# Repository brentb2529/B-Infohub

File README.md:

# B-Infohub

**Local telemetry from a Briggs & Stratton standby generator — no subscription, no cell modem, no cloud.**

A small ESP32 board that plugs into the RS-485 port your generator already has and
speaks Modbus to its GC-1030/1031/1032 controller directly. Home Assistant gets the
readings in about a second, over your own network.

> The InfoHub is not decoding anything proprietary. It is a Modbus master with a cell
> modem and a billing relationship attached. This becomes the master instead — and you
> can keep the InfoHub connected alongside it if you want the cellular path as backup.

---

## What you get

| | EnergyTrak cloud | B-Infohub |
| --- | --- | --- |
| Readings | 34 | **130+** |
| Freshness | minutes | **~1 second** |
| Faults | one "fault" flag | **34 individually decoded alarms** |
| Works without internet | no | **yes** |
| Subscription | yes | no |

Per-leg voltages and currents, kW / kVA / kVAr, power factor, cumulative energy,
coolant temperature, battery voltage, engine RPM and hours, lifetime starts and trips,
the raw controller status word, and each fault condition as its own entity you can
automate on.

It also records alarms to onboard flash, so a fault that happens while Home Assistant
is down or the network is out is still reported when things come back — the one case
cloud monitoring cannot cover.

## What you need

- A Briggs & Stratton standby generator with a **GC-1030, GC-1031 or GC-1032**
  controller (check the label on the panel).
- A **B-Infohub board** — see [Getting the hardware](#getting-the-hardware).
- Home Assistant, with [HACS](https://hacs.xyz) installed.
- A Chrome or Edge browser on a desktop, once, to flash the board.

No soldering. No toolchain. No command line.

## Install

### 1. Flash the board

Connect it to your computer with a **data** USB cable and open the installer:

### → **[Install B-Infohub](https://brentb2529.github.io/B-Infohub/)**

Click Connect, pick the serial port, and wait. The page will then ask for your Wi-Fi.

<sub>A charge-only USB cable is the most common reason nothing appears in the port list —
it powers the board but carries no data, so the board looks dead to the browser while its
power light is on. Web Serial needs Chrome or Edge; Safari and Firefox do not implement it.</sub>

### 2. Wire it to the generator

**Switch the generator to OFF at the panel first.** Two wires, into the RS-485
terminals the controller already exposes — [wiring guide](docs/wiring.md), including
where the terminals are on each controller and how to keep an existing InfoHub
connected at the same time.

### 3. Add it to Home Assistant

Install the **[EnergyTrak integration](https://github.com/brentb2529/ha-energytrak)**
from HACS, then **Settings → Devices & Services → Add Integration → EnergyTrak**.

The bridge is discovered automatically if it is on the same subnet. On a routed or
VLAN'd network — which includes most setups where the generator is on a different
segment — choose **Local B-Infohub bridge** and enter its IP.

You do **not** need an EnergyTrak account. The integration supports three shapes:

- **Bridge only** — no subscription at all
- **Cloud only** — the original behaviour, no hardware
- **Both** — the bridge is used while it is healthy, and the cloud takes over
  automatically if it is not

## Getting the hardware

The board is built in small batches and is **not sold through a shop**. If you want
one, open a [GitHub issue](https://github.com/brentb2529/B-Infohub/issues) or get in
touch — see the ordering note below.

<!-- ORDERING DETAILS: fill these in before publishing.
     - How should people contact you (issue / email / form)?
     - What is supplied: bare PCB, assembled board, assembled + enclosure?
     - Price, and whether shipping is US-only.
     - Any lead time or batch-size caveat. -->

> **Ordering:** _contact details and what is supplied to be filled in._

Everything needed to have one made independently is in this repository —
schematic, layout, gerbers and a JLCPCB-ready fab package in
[`hardware/pcb/`](hardware/pcb/) — and the firmware is MIT licensed. Buying a board
is a convenience, not a requirement.

## It learns the generator it is plugged into

On first healthy contact the bridge probes the controller once — what it
answers, which alarm inputs are wired — and publishes a **Controller
Profile**. Home Assistant shows the learned family as the device model,
plus *Registers present*, *Alarm inputs indeterminate* and *Commissioned*.
**Run Discovery** repeats it. See [`docs/discovery.md`](docs/discovery.md).

## If something looks wrong

The bridge reports its own health, because a monitor that fails silently is worse
than no monitor:

| Entity | What it means when it is unhappy |
| --- | --- |
| **Bridge reachable** | the board is not answering Home Assistant — power or Wi-Fi |
| **Generator answering bus** | the board is fine; the generator has gone quiet on RS-485 |
| **Controller clock age** | the controller is answering but its clock has stopped — it has hung |
| **Bridge silence** | the board holds its connection but has stopped sending |
| **Wi-Fi Signal** | below about −72 dBm an ESP32 stays associated but cannot be reached |

Those are deliberately five separate signals rather than one "online" flag. They fail
independently and each one points at a different place to look.

There are also five LEDs on the board readable through the lid, which is all you have
standing at the generator with no phone signal. [How to read
them](docs/bring-up.md#status-leds).

## Documentation

| | |
| --- | --- |
| [Wiring](docs/wiring.md) | terminals, cable, termination, keeping the InfoHub |
| [Bring-up](docs/bring-up.md) | first boot, LEDs, proving the bus |
| [Register map](docs/register-map.md) | every address, what it means, what it returns |
| [Field findings](docs/field-findings-2026-08-31.md) | what a real controller actually answers |
| [Development](docs/development.md) | building the firmware, the contract, the tooling |

## Safety and scope

A standby generator is life-safety equipment. This is a **read-only monitor**: it does
not start, stop, or configure anything, and engine control is deliberately not
implemented.

Do not rely on it as your only alerting for anything that matters. It is unofficial,
unaffiliated with Briggs & Stratton, and provided as-is under the MIT licence with no
warranty. Wiring anything into a generator is your responsibility; if you are not
comfortable working in the panel, have an electrician do it.

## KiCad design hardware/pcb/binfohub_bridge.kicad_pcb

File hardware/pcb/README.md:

# B-Infohub Bridge v1.1 — PCB

90 × 92 mm, 2-layer, 1.6 mm FR4. KiCad 10 project generated programmatically from
`tools/circuit.py` and verified with `kicad-cli` 10.0.5.

> **Rev 1.1 (2026-10-01) is the current design**: schematic, board, routing, BOM,
> gerbers and the checks below are all rev 1.1. **It fits the rev 1.0 enclosure
> unchanged** — same outline, same six M3 holes, same three terminals on the top
> edge, same LED light-pipe positions. What changed, and why, is in *Rev 1.1*
> below. Rev 1.0 is the fielded board (one unit, running since 2026-09); its files
> are in git history at tag `pcb-rev1.0`.

## Rev 1.1

| Change | Why |
| --- | --- |
| **ESP32-WROOM-32E-H4 soldered**, replacing the socketed DevKitC | Heat. The fielded unit's die ran 125–135 °F at night and 188 °F in afternoon sun, and at 188 °F the controller link dropped a byte per reply (see *Heat*). The -H4 is the −40…+105 °C grade (the plain -32E is rated to 85 °C — the temperature this board has already reached). The DevKit's AMS1117 (5→3.3 V linear, ~0.3 W inside the module footprint) is gone; the module sits on a via-stitched ground pad. |
| **DE pull-downs** (R16/R17, EE review) | The SP3485's DE input has no pull-down and the ESP's GPIOs float from reset until the firmware runs — and for the whole of a J6 first flash. 10 k on each DE keeps both transceivers in receive, so the board can never drive the generator's bus uncommanded. Rev 1.0 is fielded without them. |
| **Single 3.3 V rail** from an AP63203 | The 5 V rail only ever fed that LDO and the PWR LED. Same buck family, pinout and application circuit as the AP63205 it replaces. |
| **Remote-antenna option**: the same pads take the **-32UE** (U.FL) | Antenna end faces the board edge, so only the enclosure wall is in front of it. Order -32E for the internal antenna; -32UE plus a U.FL→SMA bulkhead pigtail if the box is metal or the signal is poor. |
| **J5 fan header**, 12 V PWM (IO32 → AO3400A), 0.5 A polyfuse, SS14 flyback | Only if shading and venting the enclosure are not enough. Firmware `packages/fan.yaml` runs it from the die temperature, Home Assistant or not. |
| **EN/IO0 support, RESET + BOOT buttons, J6 programming header** | A bare module has no USB bridge; J6 is the one USB-serial flash it ever needs. OTA after that, as before. |
| **R10/R11** fail-safe bias on the InfoHub pair | Carried from the 2026-09-28 source-only change — see *Termination*. |
| LED series resistors moved 75 → 77.5 mm; J4 moved to the left edge | Clearing the module's pad row and the antenna region. LEDs themselves have not moved. |

Replaces the Briggs & Stratton InfoHub as the Modbus master on the GC-1032's RS-485
bus, **while passing the InfoHub through on a second port** so its cell modem keeps
working as out-of-band backup during an outage.

| Check (rev 1.1, 2026-10-01) | Result |
| --- | --- |
| `kicad-cli sch erc --severity-all` | **0 violations** (`binfohub_bridge-erc.rpt`) |
| `kicad-cli pcb drc --severity-all --refill-zones --schematic-parity` | **0 errors, 0 unconnected, 0 parity issues** |
| Routing | **100 %**, 0.25 mm-grid A* router, 738 tracks / 109 vias, GND pour both layers **plotted into the gerbers** (see below) |
| LCSC | **36 distinct parts**, one BOM line each; the 11 parts new or changed in rev 1.1 verified in stock on 2026-10-01, the rest last checked 2026-08-31 |

Remaining DRC output is a handful of warnings: short dangling tails on hand-routed
escape stubs the router joined part-way along (low-speed lines, verified
electrically meaningless in the EE review), and `lib_footprint_mismatch` on the
terminal blocks (locating pegs deliberately stripped, see ORDER.md) and on U1
(the project copy of the WROOM footprint, identical to the library on every
pad, via and keepout). **No silk over any pad, no courtyard overlaps.** The exact
counts are in `binfohub_bridge-drc.rpt`.

**EE review (2026-10-01):** independent pre-fab review of the full source; verdict
*green after fixes*, all applied — -H4 module, DE pull-downs, 680 Ω bias, 1.1 A fan
fuse, 100 nF moved to the VDD pad, BOM grouping by part, JLC gerber layer set.
Confirmed clean: every pin against the firmware map, no strapping pins, EN/IO0
reference circuit, buck pinout and FB, D10/Q2 polarity, SM712 pin order, pour
present in the gerbers, antenna keepout honoured.

> **Rev 1.0's shipped gerbers had no ground pour.** `gen_pcb.py` writes zone
> outlines only, and the rev 1.0 plot never refilled them: the F_Cu gerber in git
> history has zero `G36` regions. The fielded board's GND is tracks only — it works,
> but it is not what the README claimed. `tools/export.sh` now plots with
> `--check-zones` and prints the region count so this cannot silently recur.

Everything is regenerated by `tools/export.sh` after `router.py` (or `rebuild.py`
for text-only changes): ERC, DRC, BOM/CPL, gerbers + drill, the JLC zip and the
previews.

## What is on it

| Block | Parts |
| --- | --- |
| **Power in** | J1 screw terminal, AO3401A reverse-polarity P-FET (4 A — carries the InfoHub too), **SMBJ16A TVS**, 100 µF bulk |
| **3.3 V rail** | AP63203WU-7 sync buck, 3.8–32 V in, fixed 3.3 V 2 A + 10 µH shielded inductor (the b-hydro / rev 1.0 circuit; the datasheet's 3.3 V example is 4.7 µH, 10 µH is the conservative side), 1.1 A polyfuse |
| **InfoHub 12 V** | Separate 2 A polyfuse (F2) |
| **Fan 12 V** | J5, separate 1.1 A / 33 V polyfuse (F3 — a PPTC derates ~40 % at box temperature, so 0.5 A would nuisance-trip), AO3400A low-side PWM switch, SS14 flyback |
| **RS-485 × 2** | SP3485EN transceivers, PSM712 TVS per pair, 120 Ω termination on jumpers (ship OPEN — see below); 680 Ω fail-safe bias R10/R11 on the InfoHub pair; 10 k pull-downs on both DE lines so neither transceiver can drive while the ESP is in reset or being flashed |
| **MCU** | ESP32-WROOM-32E**-H4** (−40…+105 °C grade) soldered, or -32UE for U.FL; 10 k/1 µF on EN, RESET and BOOT buttons, J6 programming header |
| **Indicators** | 5 LEDs (PWR / WIFI / BUS / FAULT / TX) sized for light pipes, plus J4 header |

### Why the power section is split into two fuses

Our bridge draws ~150 mA. The InfoHub's cell modem pulses to 1–2 A on transmit. Sharing
a fuse would let an InfoHub fault take down the telemetry — precisely backwards. Both
legs sit behind the same reverse-polarity FET, so a miswired harness cannot hurt either
device, but a fault in one cannot starve the other.

### Why the LED resistors are 100R / 330R and not 1k

These are driven from a 3.3 V GPIO. A blue or green LED has a forward drop near 2.9 V,
leaving ~0.4 V across the resistor — 1k would give roughly **0.5 mA**, invisible through
a light pipe. 100R for blue/green and 330R for red/yellow puts all five at about 4 mA.

## Termination: ship JP1 and JP2 OPEN

Measured, not assumed. On 2026-08-31 the live bus delivered **368 consecutive
error-free 87-register block reads** (32,016 values, every one CRC-checked) across
engine cranking and five minutes of running, with an adapter that was almost certainly
unterminated. Zero failures.

The physics agrees. At 9600 baud one bit is **104 µs**; signal propagates at ~5 ns/m,
so even a 30 m run has a 150 ns round trip — 0.14 % of a bit period. Reflections from
the SP3485's fast edges settle within a few hundred nanoseconds, while the receiver
samples in the *middle* of the bit. Termination is governed by edge rate versus cable
delay, and here there are three orders of magnitude of margin.

There is also a cost to fitting them: 120 Ω with no fail-safe biasing pulls A and B
together at idle, which can leave the receiver output indeterminate and produce framing
errors. **Adding termination to a bus that already works can make idle behaviour
worse.**

So: leave both jumpers open. Fit one only if CRC errors appear on that segment. They
exist so the option is available, not because it is needed.

If a bus ever does misbehave at idle rather than in traffic, the fix is fail-safe
biasing (pull-up on A, pull-down on B), not termination.

**Rev 1.0 has no bias footprints, and port B does misbehave at idle.** A raw-frame
capture on 2026-09-28 showed ~61 bytes of garbage arriving on the InfoHub pair 35–57 ms
after every reply the bridge sends — the pair floating inside the receiver's ±200 mV
dead band once our driver releases it. ESPHome's Modbus server reads that as an
incoming request, holds its next reply, and drops it: 8 of 36 replies to the InfoHub
in 75 s, with the InfoHub retrying after 0.8 s each time. It tolerates this (it kept
the vendor cloud fed for a week on it), but the bus is dirtier than it should be. Port
A is unaffected because the GC-1032 biases its own bus.

**Rev 1.1 adds R10/R11** (4.7 kΩ pull-up on A to 3.3 V, pull-down on B to GND, next
to U4), fitted by default. Rev 1.0 boards are left as they are by decision; the
firmware can be made tolerant of the noise (flush the port-B receive buffer after
transmitting) if a fielded board ever needs it.

## Heat — measured on the fielded unit, 2026-10-01

The ESP32 die runs **125–135 °F at night** with the air in the 50s: ~75 °F of
self-heating in a sealed box with no airflow. A clear afternoon adds **45–60 °F**
of solar gain on the enclosure (overcast days add 8–17 °F), and the peak is always
13:30–14:45 regardless of the air temperature. On 1 Oct, 80 °F air put the die at
**188 °F**; the port-A link to the GC-1032 then dropped one byte from every reply
(0 good reads for ~90 min, reproduced on a fresh boot at the same temperature) and
recovered on its own as the box cooled. 185 °F on 25 Sep had survived, so the cliff
is ~185–188 °F die. Which end of the link drifts first is not known; the SP3485EN
is industrial grade (−40…+85 °C), the controller is in the same sun.

Firmware 1.2.1 took the two biggest self-heat terms down (CPU 240→160 MHz, Wi-Fi
modem sleep): die fell 192→162 °F in four minutes in the same sun. HA automation
`binfohub_bridge_hot` warns at 175 °F. Neither is the fix; the enclosure is.

**In order of effect:**

1. **Mounting note on the enclosure and in the install guide: not in direct
   afternoon sun.** Shade (a louvered shroud, or the north side of the pad) is
   worth more than every item below combined — it is the ~55 °F term.
2. **A breathing enclosure.** The rev 1.0 box has one membrane vent, low, and
   still reached 188 °F: one vent does not convect. Add a second Gore-type vent
   **high** on the opposite wall so the box is a chimney. Passive; no moving parts
   on a box that must run through an outage.
3. **Done in rev 1.1: bare ESP32-WROOM-32E on the board, 3.3 V straight from an
   AP63203 buck.** The DevKit's AMS1117 LDO dissipated ~0.3 W dropping 5→3.3 V
   inside the module footprint; the module now sits on a via-stitched ground pad
   into the back-side pour.
4. **Fan — provided for, not fitted.** Rev 1.1 carries J5 (12 V, PWM, fused,
   flyback) so a fan can be added without a board change if 1–3 are not enough.
   A fan is a moving part, a dust and moisture path, and a load on the
   generator-side 12 V; a heatsink in still, trapped air moves heat into the same
   air. Neither is the first answer.

Acceptance test: a sunny-afternoon die peak at least 20 °F under the 175 °F
alert, i.e. the rev 1.1 unit should never page.

## Bus parameters — measured, not assumed

**Slave 10, 9600 8E1.** Not the genmon defaults (1 / 19200). Found with
`tools/gc1032_probe.py scan` on 2026-08-31 and confirmed against live readings; the
values are on the back silkscreen so nobody has to re-derive them. See
`../../docs/field-findings-2026-08-31.md`.

## Enclosure interface

The lid needs light pipes over these LED centres (board coordinates, origin = top-left):

| LED | Function | Colour | x | y |
| --- | --- | --- | --- | --- |
| D5 | PWR | green | 18.0 | 80.0 |
| D6 | WIFI | blue | 29.0 | 80.0 |
| D7 | BUS | green | 40.0 | 80.0 |
| D8 | FAULT | red | 51.0 | 80.0 |
| D9 | TX | yellow | 62.0 | 80.0 |

11 mm pitch, which suits 3 mm acrylic rod.

**Cable entry.** All three terminals sit on the **top edge (y = 7)** with their wire
openings facing outward, so one enclosure wall takes every gland. Pad spans:

| Terminal | x range |
| --- | --- |
| J1 12 V IN (2P, 5.08 mm) | 12.0 – 17.1 |
| J2 BUS (2P, 2.54 mm) | 50.0 – 52.5 |
| J3 INFOHUB (4P, 2.54 mm) | 70.0 – 77.6 |

**Terminal contents.** The generator harness carries four conductors that matter:
+12 V, GND, and the RS-485 pair. Power lands on J1, the pair lands on J2 — and J2
needs no ground pin of its own, because the harness ground is already on J1 and it is
the same net. J3 is different: it is a separate cable run out to the InfoHub carrying
power *and* data, so it needs its own return.

| | Pins | To |
| --- | --- | --- |
| J1 | +12V, GND | harness power (red/grey, black) |
| J2 | A, B | harness RS-485 pair (brown, yellow) |
| J3 | +12V, GND, A, B | the InfoHub |

**Mounting:** six M3 holes at (4.5, 4.5), (85.5, 4.5), (4.5, 46), (85.5, 46),
(4.5, 87.5), (85.5, 87.5).

## Files

| File | Purpose |
| --- | --- |
| `binfohub_bridge.kicad_pro/.kicad_sch/.kicad_pcb` | KiCad project |
| `binfohub.kicad_sym`, `binfohub.pretty/` | ESP32-DevKitC-38 symbol + footprint |
| `binfohub_bridge_jlc.zip` | Gerber X2 + Excellon — upload as-is |
| `bom_jlc.csv`, `cpl_jlc.csv` | JLCPCB BOM (verified LCSC numbers) and pick-and-place |
| `ORDER.md` | What to upload, board options, and the loose parts JLC will not place |
| `preview/silk_front-1.png` | Readable silkscreen plot |
| `preview/top.png`, `schematic.pdf` | Render and schematic |
| `tools/` | `circuit.py` is the single source of truth |

Regenerate: `cd tools && python3 gen_libs.py && python3 gen_sch.py && python3 router.py && python3 gen_bom.py`

## Two fixes made to the inherited b-hydro tooling

**`router.py` — trapped-pad escapes.** A pad ringed by its neighbours' keepouts
(SOIC-8 at 1.27 mm, TSOT-23-6) has no free cell for A* to start from. `prelinks`
extended only the *target* set, which helps the far end of a net and does nothing for
the pad that is actually stuck. It now seeds the *source* side too. This took routing
from 11 failures to 0.

**`router.py` — mounting keepouts.** Were hard-coded to b-hydro's 120 × 90 corners, so
two keepouts sat off this board and two real holes had none.

## Before ordering

Not yet reviewed by a second pair of eyes. Specifically worth checking:

- **SM712 pin mapping.** KiCad's `SM712_SOT23` symbol has pin 3 as common; confirm
  against the PSM712 datasheet before fab. Getting it wrong makes the TVS useless.
- Terminal-block orientation (the 180° post-pass in `circuit.py`) — this is the exact
  issue JLC's DFM review flagged on b-hydro.
- AP63205 application circuit against its datasheet, though it is unchanged from a
  board that has already been built.

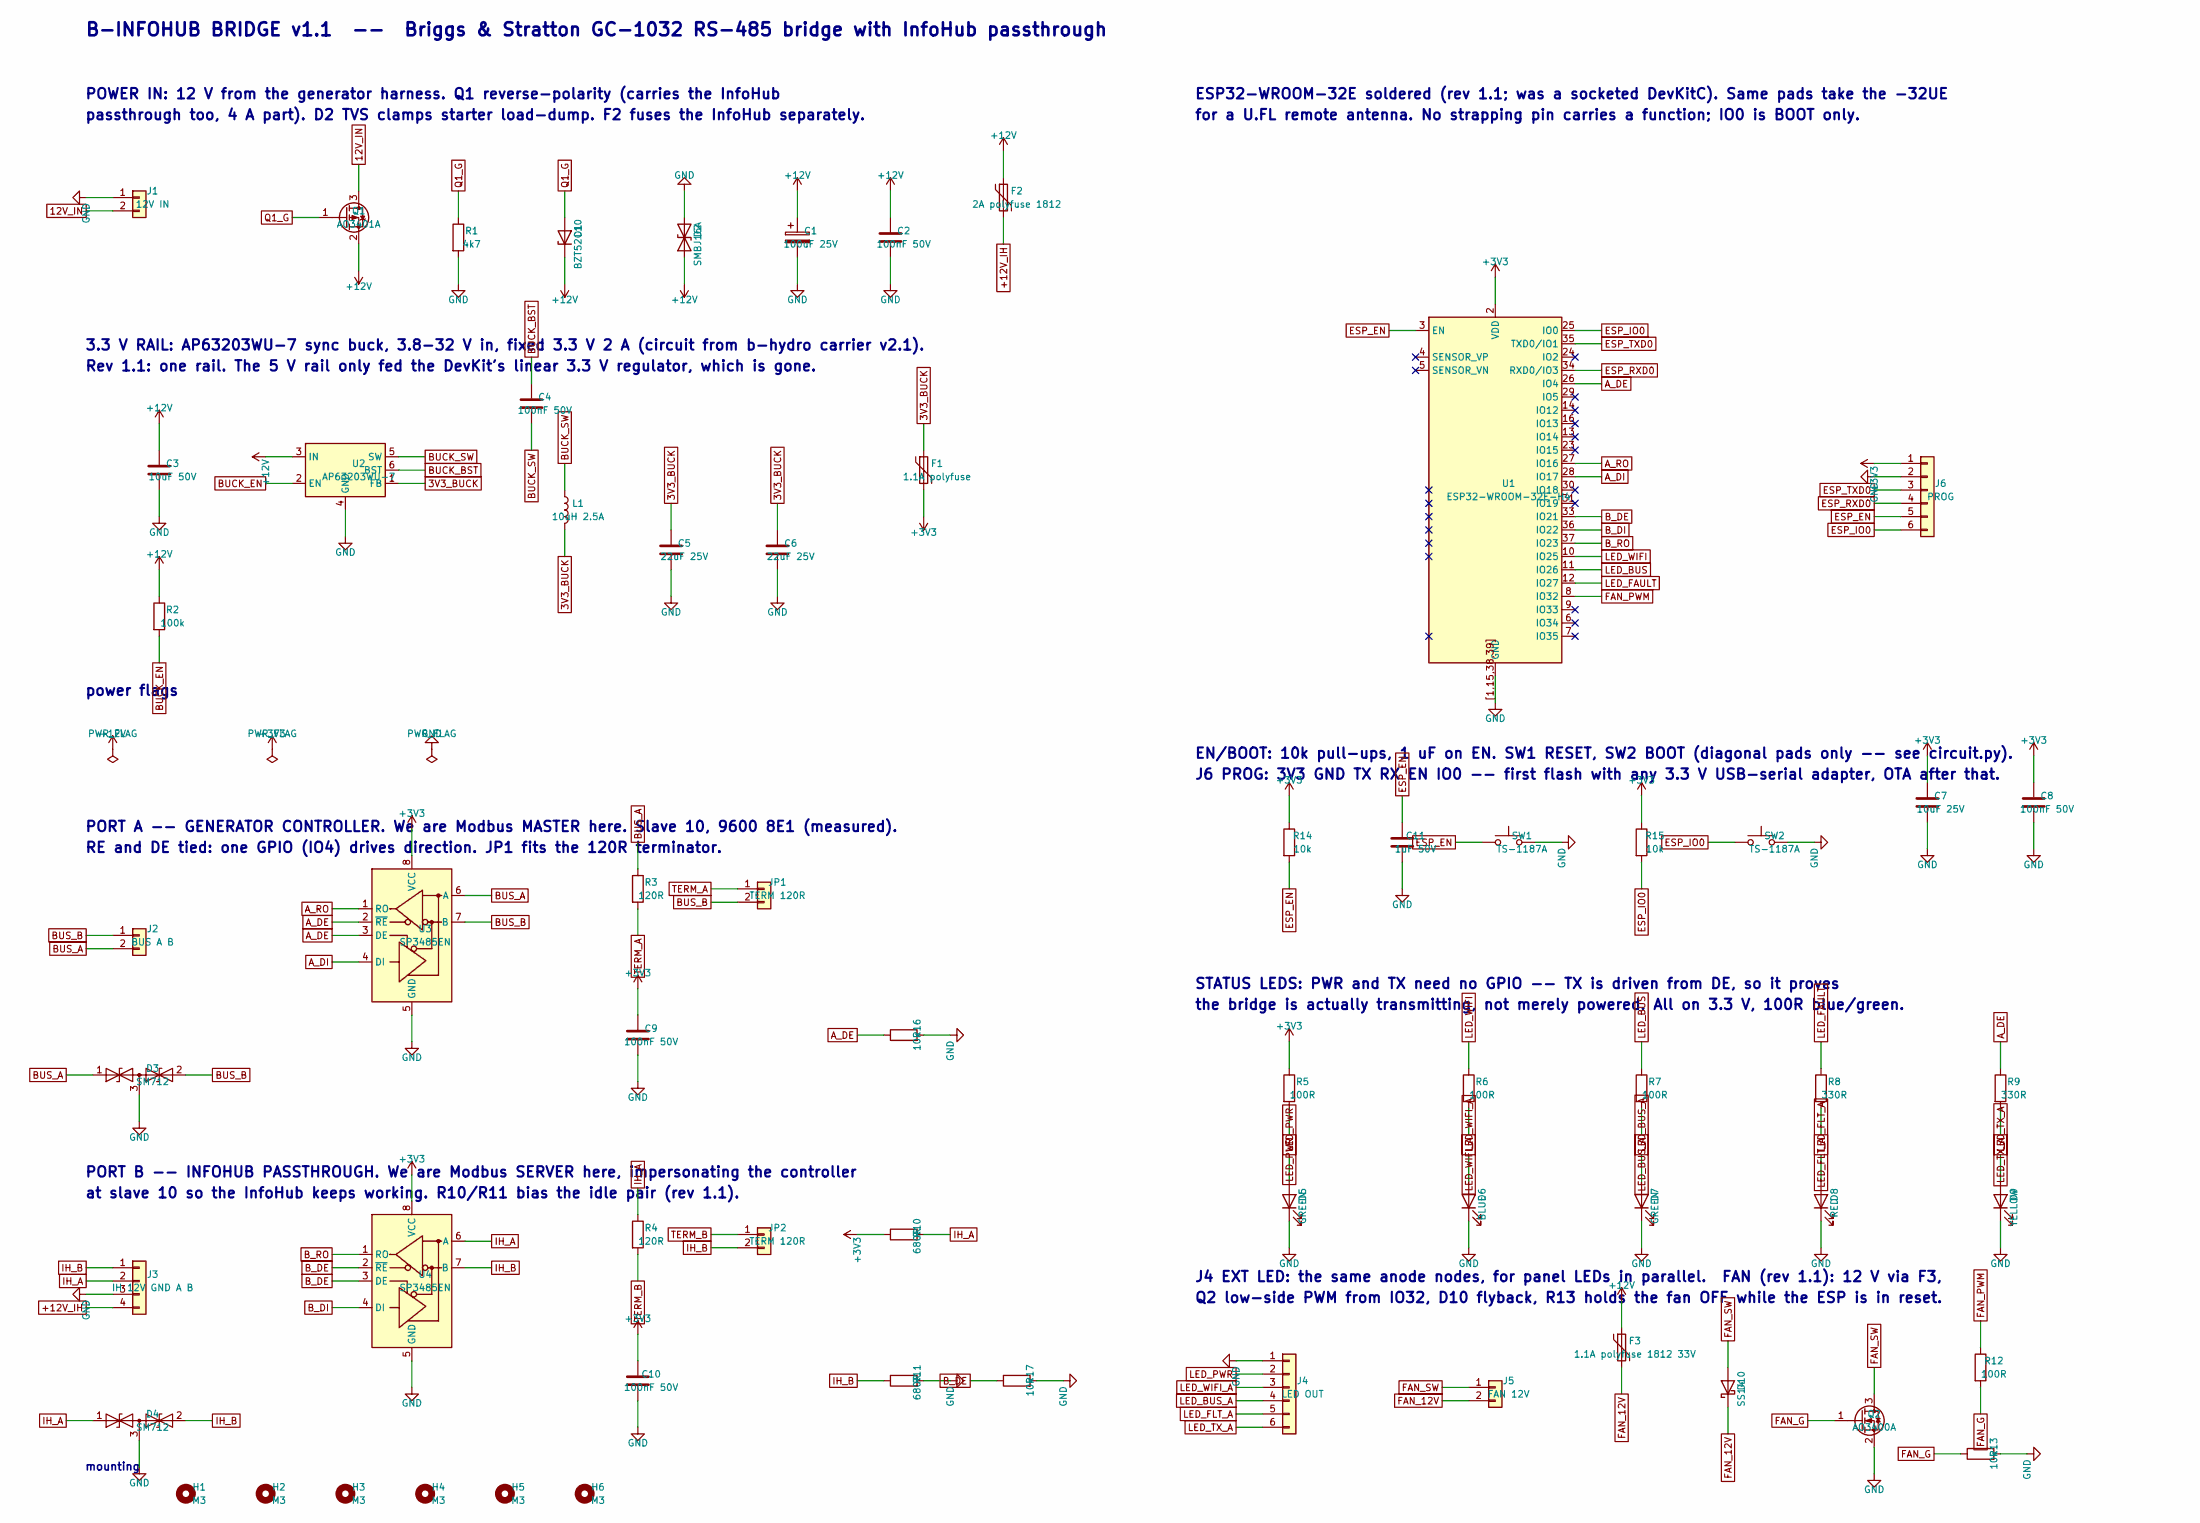
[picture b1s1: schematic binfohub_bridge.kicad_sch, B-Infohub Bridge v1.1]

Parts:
C1: 100uF 25V; CP_Elec_6.3x7.7; LCSC C3338
C2, C4, C8, C9, C10: 100nF 50V; C_0603_1608Metric; LCSC C14663
C3: 10uF 50V; C_1206_3216Metric; LCSC C13585
C5, C6: 22uF 25V; C_0805_2012Metric; LCSC C45783
C7: 10uF 25V; C_0805_2012Metric; LCSC C15850
C11: 1uF 50V; C_0603_1608Metric; LCSC C15849
D1: BZT52C10; D_SOD-123; LCSC C173431
D2: SMBJ16A; D_SMB; LCSC C353386
D3, D4: SM712; SOT-23; LCSC C32677
D5, D7: GREEN; LED_0603_1608Metric; LCSC C965804
D6: BLUE; LED_0603_1608Metric; LCSC C965807
D8: RED; LED_0603_1608Metric; LCSC C2286
D9: YELLOW; LED_0603_1608Metric; LCSC C965803
D10: SS14; D_SMA; LCSC C2480
F1: 1.1A polyfuse; Fuse_1812_4532Metric; LCSC C883148
F2: 2A polyfuse 1812; Fuse_1812_4532Metric; LCSC C2760293
F3: 1.1A polyfuse 1812 33V; Fuse_1812_4532Metric; LCSC C142747
H1, H2, H3, H4, H5, H6: M3; MountingHole_3.2mm_M3
J1: 12V IN; TerminalBlock_Phoenix_MKDS-1,5-2-5.08_1x02_P5.08mm_Horizont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; LCSC C474881
J2: BUS A B; TerminalBlock_Phoenix_MPT-0,5-2-2.54_1x02_P2.54mm_Horizontal; LCSC C474920
J3: IH 12V GND A B; TerminalBlock_Phoenix_MPT-0,5-4-2.54_1x04_P2.54mm_Horizontal; LCSC C474922
J4: LED OUT; PinHeader_1x06_P2.54mm_Vertical; LCSC C492405
J5: FAN 12V; TerminalBlock_Phoenix_MPT-0,5-2-2.54_1x02_P2.54mm_Horizontal; LCSC C474920
J6: PROG; PinHeader_1x06_P2.54mm_Vertical; LCSC C492405
JP1, JP2: TERM 120R; PinHeader_1x02_P2.54mm_Vertical; LCSC C492401
L1: 10uH 2.5A; L_Bourns_SRN6045TA; LCSC C79272
Q1: AO3401A; SOT-23; LCSC C15127
Q2: AO3400A; SOT-23; LCSC C20917
R1: 4k7; R_0603_1608Metric; LCSC C23162
R2: 100k; R_0603_1608Metric; LCSC C25803
R3, R4: 120R; R_0603_1608Metric; LCSC C22787
R5, R6, R7, R12: 100R; R_0603_1608Metric; LCSC C22775
R8, R9: 330R; R_0603_1608Metric; LCSC C23138
R10, R11: 680R; R_0603_1608Metric; LCSC C23228
R13, R14, R15, R16, R17: 10k; R_0603_1608Metric; LCSC C25804
SW1, SW2: TS-1187A; SW_TS-1187A; LCSC C318884
U1: ESP32-WROOM-32E-H4; ESP32-WROOM-32E_edge; LCSC C3013935
U2: AP63203WU-7; TSOT-23-6; LCSC C780769
U3, U4: SP3485EN; SOIC-8_3.9x4.9mm_P1.27mm; LCSC C8963

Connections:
3V3_BUCK: C5.1, C6.1, F1.1, L1.2, U2.1 (FB)
12V_IN: J1.2, Q1.3 (D)
+3V3: C7.1, C8.1, C9.1, C10.1, F1.2, J6.1, R5.1, R10.1, R14.1, R15.1, U1.2 (VDD), U3.8 (VCC), U4.8 (VCC)
+12V: C1.1, C2.1, C3.1, D1.1 (K), D2.1 (A1), F2.1, F3.1, Q1.2 (S), R2.1, U2.3 (IN)
+12V_IH: F2.2, J3.4
A_DE: R9.1, R16.1, U1.26 (IO4), U3.2 (~RE), U3.3 (DE)
A_DI: U1.28 (IO17), U3.4 (DI)
A_RO: U1.27 (IO16), U3.1 (RO)
BUCK_BST: C4.1, U2.6 (BST)
BUCK_EN: R2.2, U2.2 (EN)
BUCK_SW: C4.2, L1.1, U2.5 (SW)
BUS_A: D3.1 (A1), J2.2, R3.1, U3.6 (A)
BUS_B: D3.2 (A2), J2.1, JP1.2, U3.7 (B)
B_DE: R17.1, U1.33 (IO21), U4.2 (~RE), U4.3 (DE)
B_DI: U1.36 (IO22), U4.4 (DI)
B_RO: U1.37 (IO23), U4.1 (RO)
ESP_EN: C11.1, J6.5, R14.2, SW1.1, U1.3 (EN)
ESP_IO0: J6.6, R15.2, SW2.1, U1.25 (IO0)
ESP_RXD0: J6.4, U1.34 (RXD0/IO3)
ESP_TXD0: J6.3, U1.35 (TXD0/IO1)
FAN_12V: D10.1 (K), F3.2, J5.2
FAN_G: Q2.1 (G), R12.2, R13.1
FAN_PWM: R12.1, U1.8 (IO32)
FAN_SW: D10.2 (A), J5.1, Q2.3 (D)
GND: C1.2, C2.2, C3.2, C5.2, C6.2, C7.2, C8.2, C9.2, C10.2, C11.2, D2.2 (A2), D3.3 (common), D4.3 (common), D5.1 (K), D6.1 (K), D7.1 (K), D8.1 (K), D9.1 (K), J1.1, J3.3, J4.1, J6.2, Q2.2 (S), R1.2, R11.2, R13.2, R16.2, R17.2, SW1.2, SW2.2, U1.1, U1.15, U1.38, U1.39, U1.[1,15,38,39] (GND), U2.4 (GND), U3.5 (GND), U4.5 (GND)
IH_A: D4.1 (A1), J3.2, R4.1, R10.2, U4.6 (A)
IH_B: D4.2 (A2), J3.1, JP2.2, R11.1, U4.7 (B)
LED_BUS: R7.1, U1.11 (IO26)
LED_BUS_A: D7.2 (A), J4.4, R7.2
LED_FAULT: R8.1, U1.12 (IO27)
LED_FLT_A: D8.2 (A), J4.5, R8.2
LED_PWR: D5.2 (A), J4.2, R5.2
LED_TX_A: D9.2 (A), J4.6, R9.2
LED_WIFI: R6.1, U1.10 (IO25)
LED_WIFI_A: D6.2 (A), J4.3, R6.2
Q1_G: D1.2 (A), Q1.1 (G), R1.1
TERM_A: JP1.1, R3.2
TERM_B: JP2.1, R4.2

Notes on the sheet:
B-INFOHUB BRIDGE v1.1 -- Briggs & Stratton GC-1032 RS-485 bridge with InfoHub passthrough
POWER IN: 12 V from the generator harness. Q1 reverse-polarity (carries the InfoHub
passthrough too, 4 A part). D2 TVS clamps starter load-dump. F2 fuses the InfoHub separately.
3.3 V RAIL: AP63203WU-7 sync buck, 3.8-32 V in, fixed 3.3 V 2 A (circuit from b-hydro carrier v2.1).
Rev 1.1: one rail. The 5 V rail only fed the DevKit's linear 3.3 V regulator, which is gone.
power flags
PORT A -- GENERATOR CONTROLLER. We are Modbus MASTER here. Slave 10, 9600 8E1 (measured).
RE and DE tied: one GPIO (IO4) drives direction. JP1 fits the 120R terminator.
PORT B -- INFOHUB PASSTHROUGH. We are Modbus SERVER here, impersonating the controller
at slave 10 so the InfoHub keeps working. R10/R11 bias the idle pair (rev 1.1).
mounting
ESP32-WROOM-32E soldered (rev 1.1; was a socketed DevKitC). Same pads take the -32UE
for a U.FL remote antenna. No strapping pin carries a function; IO0 is BOOT only.
EN/BOOT: 10k pull-ups, 1 uF on EN. SW1 RESET, SW2 BOOT (diagonal pads only -- see circuit.py).
J6 PROG: 3V3 GND TX RX EN IO0 -- first flash with any 3.3 V USB-serial adapter, OTA after that.
STATUS LEDS: PWR and TX need no GPIO -- TX is driven from DE, so it proves
the bridge is actually transmitting, not merely powered. All on 3.3 V, 100R blue/green.
J4 EXT LED: the same anode nodes, for panel LEDs in parallel. FAN (rev 1.1): 12 V via F3,
Q2 low-side PWM from IO32, D10 flyback, R13 holds the fan OFF while the ESP is in reset.

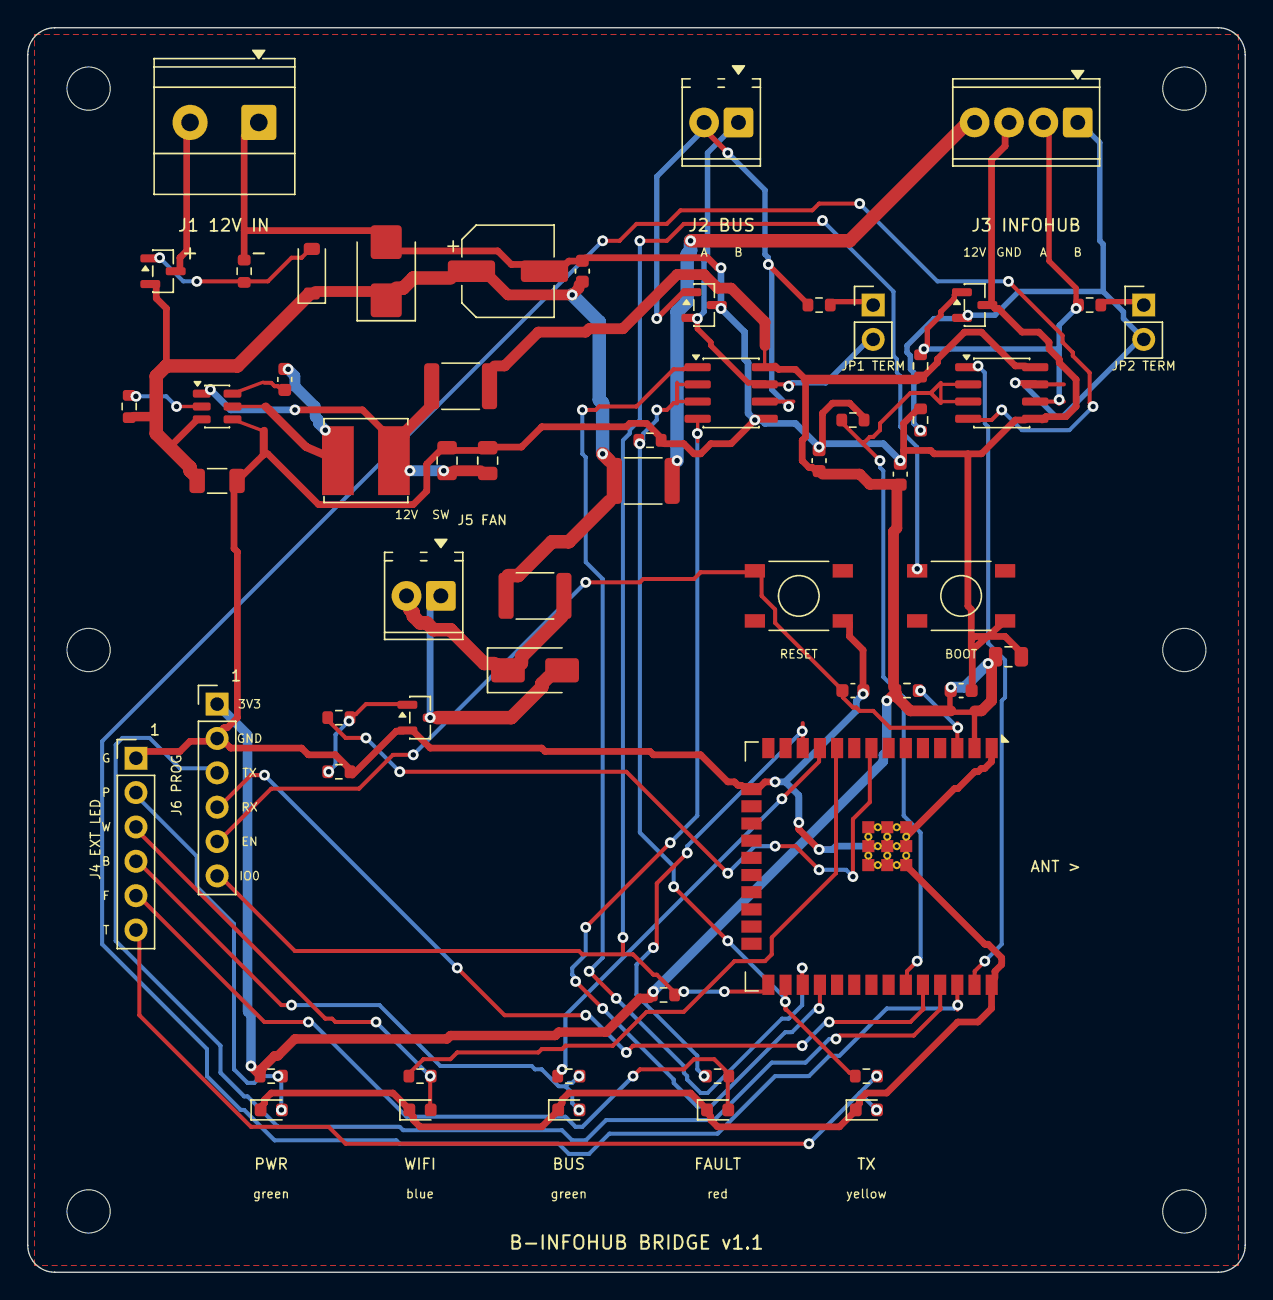
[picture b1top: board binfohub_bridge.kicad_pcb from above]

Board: 2 copper layers, 90.0 x 92.0 mm, 64 parts (0 on the bottom side), 38 nets.

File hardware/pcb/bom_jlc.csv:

Comment,Designator,Footprint,LCSC Part #,Qty,Assembly,Note,Description
100uF 25V,C1,CP_Elec_6.3x7.7,C3338,1,JLC SMT,,12 V bulk: holds the rail through the crank dip (11.4 V measured 2026-08-31)
100nF 50V,"C2,C4,C8,C9,C10",C_0603_1608Metric,C14663,5,JLC SMT,,"3.3 V HF decoupling, 4.5 mm from the VDD pad"
10uF 50V,C3,C_1206_3216Metric,C13585,1,JLC SMT,,"buck input cap, right at VIN. 50 V not 25 V: ceramics lose a lot of capacitance under DC bias, and this sits on a 14.6 V rail. (b-hydro used C89632; that part is down to single-digit stock at LCSC, so this board takes the basic-part equivalent.)"
22uF 25V,"C5,C6",C_0805_2012Metric,C45783,2,JLC SMT,,buck output cap 1
10uF 25V,C7,C_0805_2012Metric,C15850,1,JLC SMT,,3.3 V bulk near the module VDD pad
1uF 50V,C11,C_0603_1608Metric,C15849,1,JLC SMT,,EN reset RC (10k/1uF ~ 10 ms)
BZT52C10,D1,D_SOD-123,C173431,1,JLC SMT,,10 V zener gate-source: clamps Q1 Vgs within the AO3401A +-12 V limit
SMBJ16A,D2,D_SMB,C353386,1,JLC SMT,,Input TVS. b-hydro skipped this on purpose (indoor). A generator pad is not indoor: the starter is a large inductive load. 16 V standoff clears the 14.6 V charging rail.
SM712,"D3,D4",SOT-23,C32677,2,JLC SMT,,"PSM712 RS-485 TVS on the controller pair (asymmetric -7/+12 V, the RS-485 standard part)"
GREEN,"D5,D7",LED_0603_1608Metric,C965804,2,JLC SMT,,GREEN LED -- Modbus online: the controller is answering. Sits under a light pipe in the lid; see enclosure docs.
BLUE,D6,LED_0603_1608Metric,C965807,1,JLC SMT,,BLUE LED -- Wi-Fi associated. Sits under a light pipe in the lid; see enclosure docs.
RED,D8,LED_0603_1608Metric,C2286,1,JLC SMT,,RED LED -- a generator fault is active. Sits under a light pipe in the lid; see enclosure docs.
YELLOW,D9,LED_0603_1608Metric,C965803,1,JLC SMT,,"YELLOW LED -- transmit: driven from DE, so it needs no GPIO and proves the bridge is actually talking. Sits under a light pipe in the lid; see enclosure docs."
SS14,D10,D_SMA,C2480,1,JLC SMT,,"Flyback across the fan: cathode to +12 V, anode to the switched node"
1.1A polyfuse,F1,Fuse_1812_4532Metric,C883148,1,JLC SMT,,"1.1 A hold / 2.2 A trip on the 3.3 V rail, below the buck's 3.2 A limit"
2A polyfuse 1812,F2,Fuse_1812_4532Metric,C2760293,1,JLC SMT,,"SMD1812-200C-30V, 2 A hold / 4 A trip, 30 V: InfoHub supply, independent of F1"
1.1A polyfuse 1812 33V,F3,Fuse_1812_4532Metric,C142747,1,JLC SMT,,"Littelfuse 1812L110/33MR: 1.1 A hold / 1.95 A trip, 33 V. Fan supply, independent of F1/F2"
12V IN,J1,"TerminalBlock_Phoenix_MKDS-1,5-2-5.08_1x02_P5.08mm_Horizontal",C474881,1,"JLC THT (economic, hand-solder fee)",,Screw terminal 5.08 2P: +12 V (harness red/grey) and GND (harness black)
TERM 120R,"JP1,JP2",PinHeader_1x02_P2.54mm_Vertical,C492401,2,"JLC THT (economic, hand-solder fee)",,"120R termination jumper, controller side. LEAVE OPEN by default: 368 consecutive error-free block reads at 9600 8E1 on 2026-08-31 with an unterminated adapter, and at 104 us per bit reflections settle ~1000x faster than the sampling instant. Fit only if CRC errors appear."
BUS A B (FAN 12V),"J2,J5","TerminalBlock_Phoenix_MPT-0,5-2-2.54_1x02_P2.54mm_Horizontal",C474920,2,"JLC THT (economic, hand-solder fee)",,"Screw terminal 2.54 2P to the ABC controller: A and B only. The harness ground arrives on J1 and is the same net, so a separate ground pin here would be redundant. Swap A/B if the bus stays silent."
IH 12V GND A B,J3,"TerminalBlock_Phoenix_MPT-0,5-4-2.54_1x04_P2.54mm_Horizontal",C474922,1,"JLC THT (economic, hand-solder fee)",,"Screw terminal 2.54 4P to the InfoHub: +12 V (fused by F2), GND, A, B"
LED OUT (PROG),"J4,J6",PinHeader_1x06_P2.54mm_Vertical,C492405,2,"JLC THT (economic, hand-solder fee)",,"Programming header: 3V3, GND, TX0, RX0, EN, IO0. First flash only; OTA after that."
10uH 2.5A,L1,L_Bourns_SRN6045TA,C79272,1,JLC SMT,,SWPA6045S100MT shielded 6x6
AO3401A,Q1,SOT-23,C15127,1,JLC SMT,,"P-MOSFET reverse-polarity protection, 4 A -- carries BOTH our load and the InfoHub passthrough"
AO3400A,Q2,SOT-23,C20917,1,JLC SMT,,"N-MOSFET low-side fan switch, 5.7 A, logic-level gate"
4k7,R1,R_0603_1608Metric,C23162,1,JLC SMT,,Q1 gate pull-down; ~0.4 mA through D1 keeps the clamp in its characterised region
100k,R2,R_0603_1608Metric,C25803,1,JLC SMT,,buck EN pull-up (always on)
120R,"R3,R4",R_0603_1608Metric,C22787,2,JLC SMT,,"bus termination, controller side"
100R,"R5,R6,R7,R12",R_0603_1608Metric,C22775,4,JLC SMT,,"D5 series resistor, ~4 mA. Small value: blue/green Vf leaves little headroom on 3.3 V."
330R,"R8,R9",R_0603_1608Metric,C23138,2,JLC SMT,,"D8 series resistor, ~4 mA."
680R,"R10,R11",R_0603_1608Metric,C23228,2,JLC SMT,,"Fail-safe bias, InfoHub pair: pull-down on B. 680R covers an unterminated pair or a terminated far end; ~390R if both ends are terminated. Rev 1.1."
10k,"R13,R14,R15,R16,R17",R_0603_1608Metric,C25804,5,JLC SMT,,B_DE pull-down: port B transceiver in receive while the ESP is in reset or being flashed (see R16)
TS-1187A,"SW1,SW2",SW_TS-1187A,C318884,2,JLC SMT,,"RESET: pulls EN low. XKB TS-1187A-B-A-B 5.1 mm tactile, JLC basic part"
ESP32-WROOM-32E-H4,U1,ESP32-WROOM-32E_edge,C3013935,1,JLC SMT,,"ESP32-WROOM-32E-H4: 4 MB, -40..+105 C grade (the plain -32E is 85 C, and this revision exists because the die reached 87 C). Soldered module, antenna toward the board edge. Standard PCBA only at JLC. ALTERNATE: ESP32-WROOM-32UE-N4 (C2934568, 85 C grade) -- identical pads, U.FL instead of the PCB antenna; fit with a U.FL-to-SMA bulkhead pigtail through the enclosure for a remote antenna. Rev 1.1."
AP63203WU-7,U2,TSOT-23-6,C780769,1,JLC SMT,,"Sync buck 3.8-32 V in, fixed 3.3 V 2 A, TSOT-23-6. Rev 1.1: was AP63205 (5 V)."
SP3485EN,"U3,U4",SOIC-8_3.9x4.9mm_P1.27mm,C8963,2,JLC SMT,,"3.3 V half-duplex RS-485, controller side. RE and DE tied: one GPIO drives direction."
